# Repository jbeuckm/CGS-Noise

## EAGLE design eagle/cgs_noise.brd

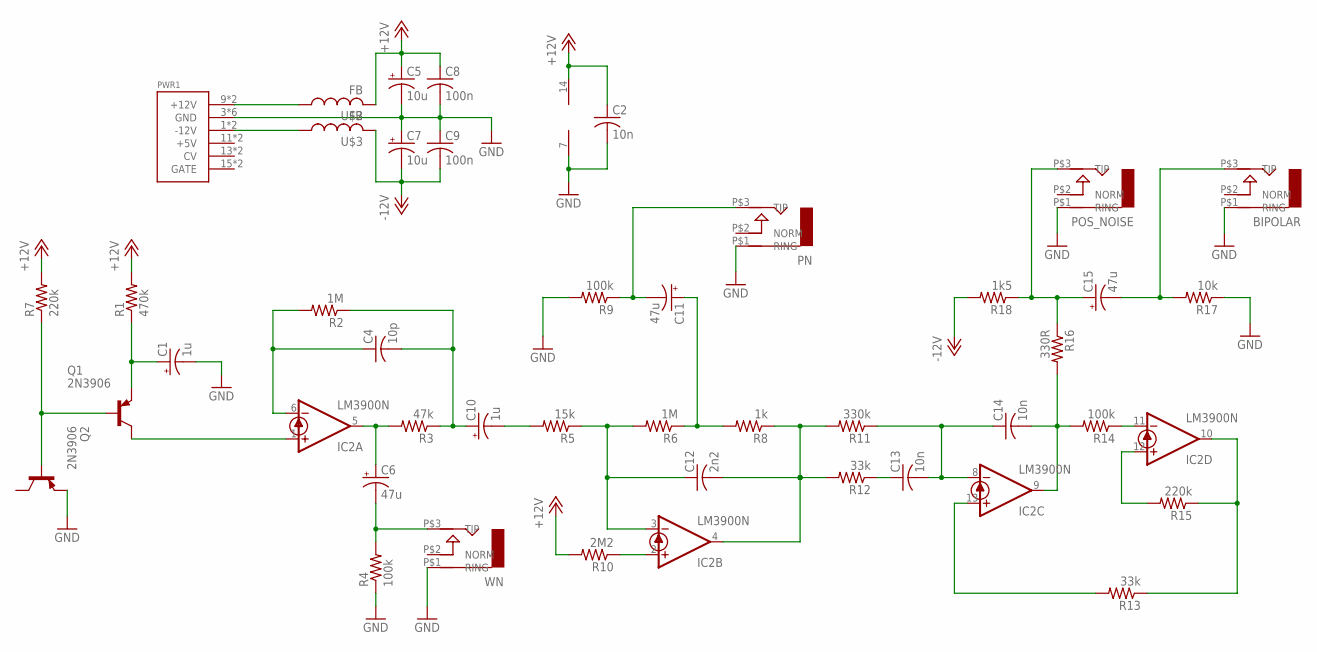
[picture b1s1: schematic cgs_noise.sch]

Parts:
BIPOLAR: AUDIO-JACK; ERTHENVAR-JACK-90DEG
C1, C10: 1u; B45181A
C2, C13, C14: 10n; C050-024X044
C4: 10p; C050-024X044
C5, C7: 10u; B45181A
C6, C11, C15: 47u; B45181A
C8, C9: 100n; C050-024X044
C12: 2n2; C050-024X044
IC2: LM3900N; DIL14
PN: AUDIO-JACK; ERTHENVAR-JACK-90DEG
POS_NOISE: AUDIO-JACK; ERTHENVAR-JACK-90DEG
PWR1: POWER; POWER_16
Q1, Q2: 2N3906; TO92
R1: 470k; 0207/10
R2, R6: 1M; 0207/10
R3: 47k; 0207/10
R4, R9, R14: 100k; 0207/10
R5: 15k; 0207/10
R7, R15: 220k; 0207/10
R8: 1k; 0207/10
R10: 2M2; 0207/10
R11: 330k; 0207/10
R12, R13: 33k; 0207/10
R16: 330R; 0207/10
R17: 10k; 0207/10
R18: 1k5; 0207/10
U$2, U$3: FB
WN: AUDIO-JACK; ERTHENVAR-JACK-90DEG

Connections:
+12V: C2.1, C5.+, C8.1, IC2.14 (V+), R1.2, R7.2, R10.2, U$2.P$2 (2)
-12V: C7.-, C9.2, R18.2, U$3.P$2 (2)
GND: BIPOLAR.P$1 (RING), C1.-, C2.2, C5.-, C7.+, C8.2, C9.1, IC2.7 (GND), PN.P$1 (RING), POS_NOISE.P$1 (RING), PWR1.3 (GND), PWR1.4 (GND), PWR1.5 (GND), PWR1.6 (GND), PWR1.7 (GND), PWR1.8 (GND), Q2.3 (E), R4.1, R9.2, R17.1, WN.P$1 (RING)
unnamed: C1.+, Q1.3 (E), R1.1
unnamed: Q1.2 (B), Q2.2 (B), R7.1
unnamed: IC2.1 (+IN), Q1.1 (C)
unnamed: C6.+, IC2.5 (OUT), R3.2
unnamed: C6.-, R4.2, WN.P$3 (TIP)
unnamed: C4.2, C10.+, R2.1, R3.1
unnamed: C4.1, IC2.6 (-IN), R2.2
unnamed: C10.-, R5.2
unnamed: C12.1, IC2.3 (-IN), R5.1, R6.2
unnamed: C11.+, R6.1, R8.2
unnamed: PWR1.9 (+12V), PWR1.10 (+12V), U$2.P$1 (1)
unnamed: C12.2, IC2.4 (OUT), R8.1, R11.2, R12.2
unnamed: IC2.13 (+IN), R13.2
unnamed: IC2.2 (+IN), R10.1
unnamed: C14.2, IC2.9 (OUT), R14.2, R16.2
unnamed: C13.2, C14.1, IC2.8 (-IN), R11.1
unnamed: C13.1, R12.1
unnamed: PWR1.1 (-12V), PWR1.2 (-12V), U$3.P$1 (1)
unnamed: IC2.11 (-IN), R14.1
unnamed: IC2.10 (OUT), R13.1, R15.1
unnamed: IC2.12 (+IN), R15.2
unnamed: BIPOLAR.P$3 (TIP), C15.-, R17.2
unnamed: C15.+, POS_NOISE.P$3 (TIP), R16.1, R18.1
unnamed: C11.-, PN.P$3 (TIP), R9.1

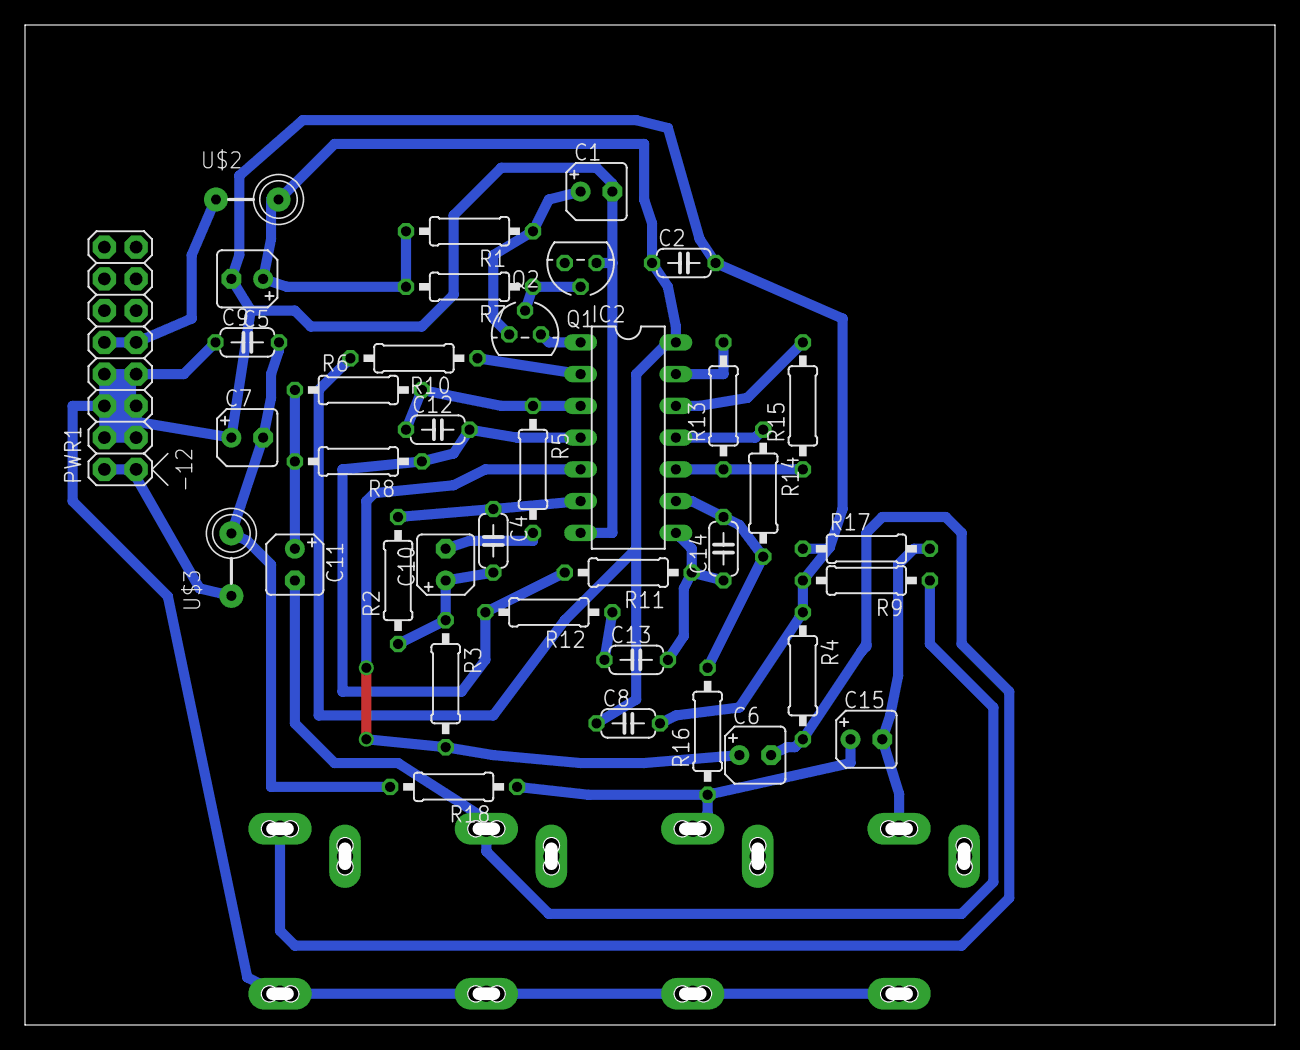
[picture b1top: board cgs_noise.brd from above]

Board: 2 copper layers, 99.0 x 79.0 mm, 42 parts (0 on the bottom side), 27 nets.

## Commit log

2016-01-05 board started
2016-01-05 almost routed
2016-01-06 routed
2016-01-09 gcode
2016-01-09 fixed shorted bypass cap trace
